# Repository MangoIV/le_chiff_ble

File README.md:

# le_chiff_ble
## What is this? 
This is a drop-in replacement PCB for [tominabox1's](https://github.com/tominabox1) Le Chiffre keyboard, one of my all time favourite boards. I redesigned the existing PCB from top up and added bluetooth. 
Please be so kind and check out the [original repo](https://github.com/tominabox1/Le-Chiffre-Keyboard) and leave a star. This is where you can also find case files for this PCB. 

Some of the footprints are not taken from the standard kicad libraries, huge thanks to [foostan](https://github.com/foostan) for making the awesome "kbd" library and to [ai03](https://ai03.com/) for their super nice footprint libraries, the minew symbol and footprints are by [oreore](https://github.com/ogatatsu).

All graphics on my PCB are hand drawn and belong to no-one but me. 

There are two PCBs in this repo one
- with hotswap, no silkscreen, see kicad/le_chiff_ble_hotswap
- without hotswap, with silkscreen, see kicad/le_chiff_ble

**I do not take any responsibility for what you do with the files supplied here in any way. Neither do I guarantee they're working for whatever purpose you intend ot use them.**

## State of the project
### implemented
- charging circuit is working
- MCU connects via bluetooth and USB
- all features have been tested and are working, including OLED and Encoder
- a working zmk firmware can be found [here](https://github.com/MangoIV/le_chiff_ble_config).
### open tasks
- the widgets in zmk for the OLED are still very basic, I'd like to do something to make them look better, this will be added after I finished and uploaded the firmware 
## How can I obtain one
- Gerbers are supplied, be free to order them from the PCB manufacturer you prefer.
### you will need parts: 
1. **Resistors, footprint is 0805:**
  - 1x 2M
  - 1x 1M
  - 1x 806k
  - 1x 100k
  - 2x 5.1k
  - 1x 1.8k 
  - 3x 1k
  - 2x 100
  - 1x 2.1
2. **Capacitors, footprint is 0805**
  - 4x 10uF
  - 2x 1uF
  - 2x 0.1uF
  - 1x 1nF
3. **Diodes**
  - 35x SOD123 for the switches and encoder
  - 1x Schottky, SOD323, should be low voltage drop
  - either 2x in switch LEDs or 2x 0805 SMD LEDs for the charging indicator
4. 1x PMOS, A03401A
5. 1x battery management chip, TP4056, footprint is SOP-8-PP
6. 1x LDO, XC6206PxxMR
7. 1x usblc6, footprint is sot-23-6
8. 1x 500mA Fuse, footprint is 1206/ 3216Metric
9. 1x battery protection IC DW01A, footprint is sot-23-6
10. 1x two nmos with gates connects FS8205, footprint is sot-23-6
11. 1x Minew MS88SF2, be careful to choose the version with nrF52840, there's also another version with the same name which won't work
12. 1x USB type c port, 12 pin
13. 1x MSK-12C02 smd toggle switch
14. 1x SW SPST TL3342 push switch for reset
15. 34-35 MX/alps/choc switches depending on whether you use the encoder or not
16. Battery connector with 1.25mm pitch, choose whichever you're fine with
17. optional: 1x Encoder, 1x 128x32 OLED
## How do I build one? 
- solder all components
- flash bootloader (I liked [this one](https://github.com/adafruit/Adafruit_nRF52_Bootloader) a lot, it's fairly easy to modify to your needs, e.g. the name the board will appear with in bootloader mode)
- plug into PC and test whether everything is working, flash Firmware 
- the firmware can be forked from [here](https://github.com/MangoIV/le_chiff_ble_config), just adjust the `.keymap` file, push, let GitHub Actions build it for you, download, done
- plug in battery, plug in PC again to unlock DW01A (this needs to be done everytime you physically disconnect the PCB from the battery)
- be careful to adjust resistor value of the tp4056 when you take different battery sizes, I chose 1Ah which works fine with the specified resistor values
- verify charging and bluetooth works 
- continue building as if this was a "normal" chiffre

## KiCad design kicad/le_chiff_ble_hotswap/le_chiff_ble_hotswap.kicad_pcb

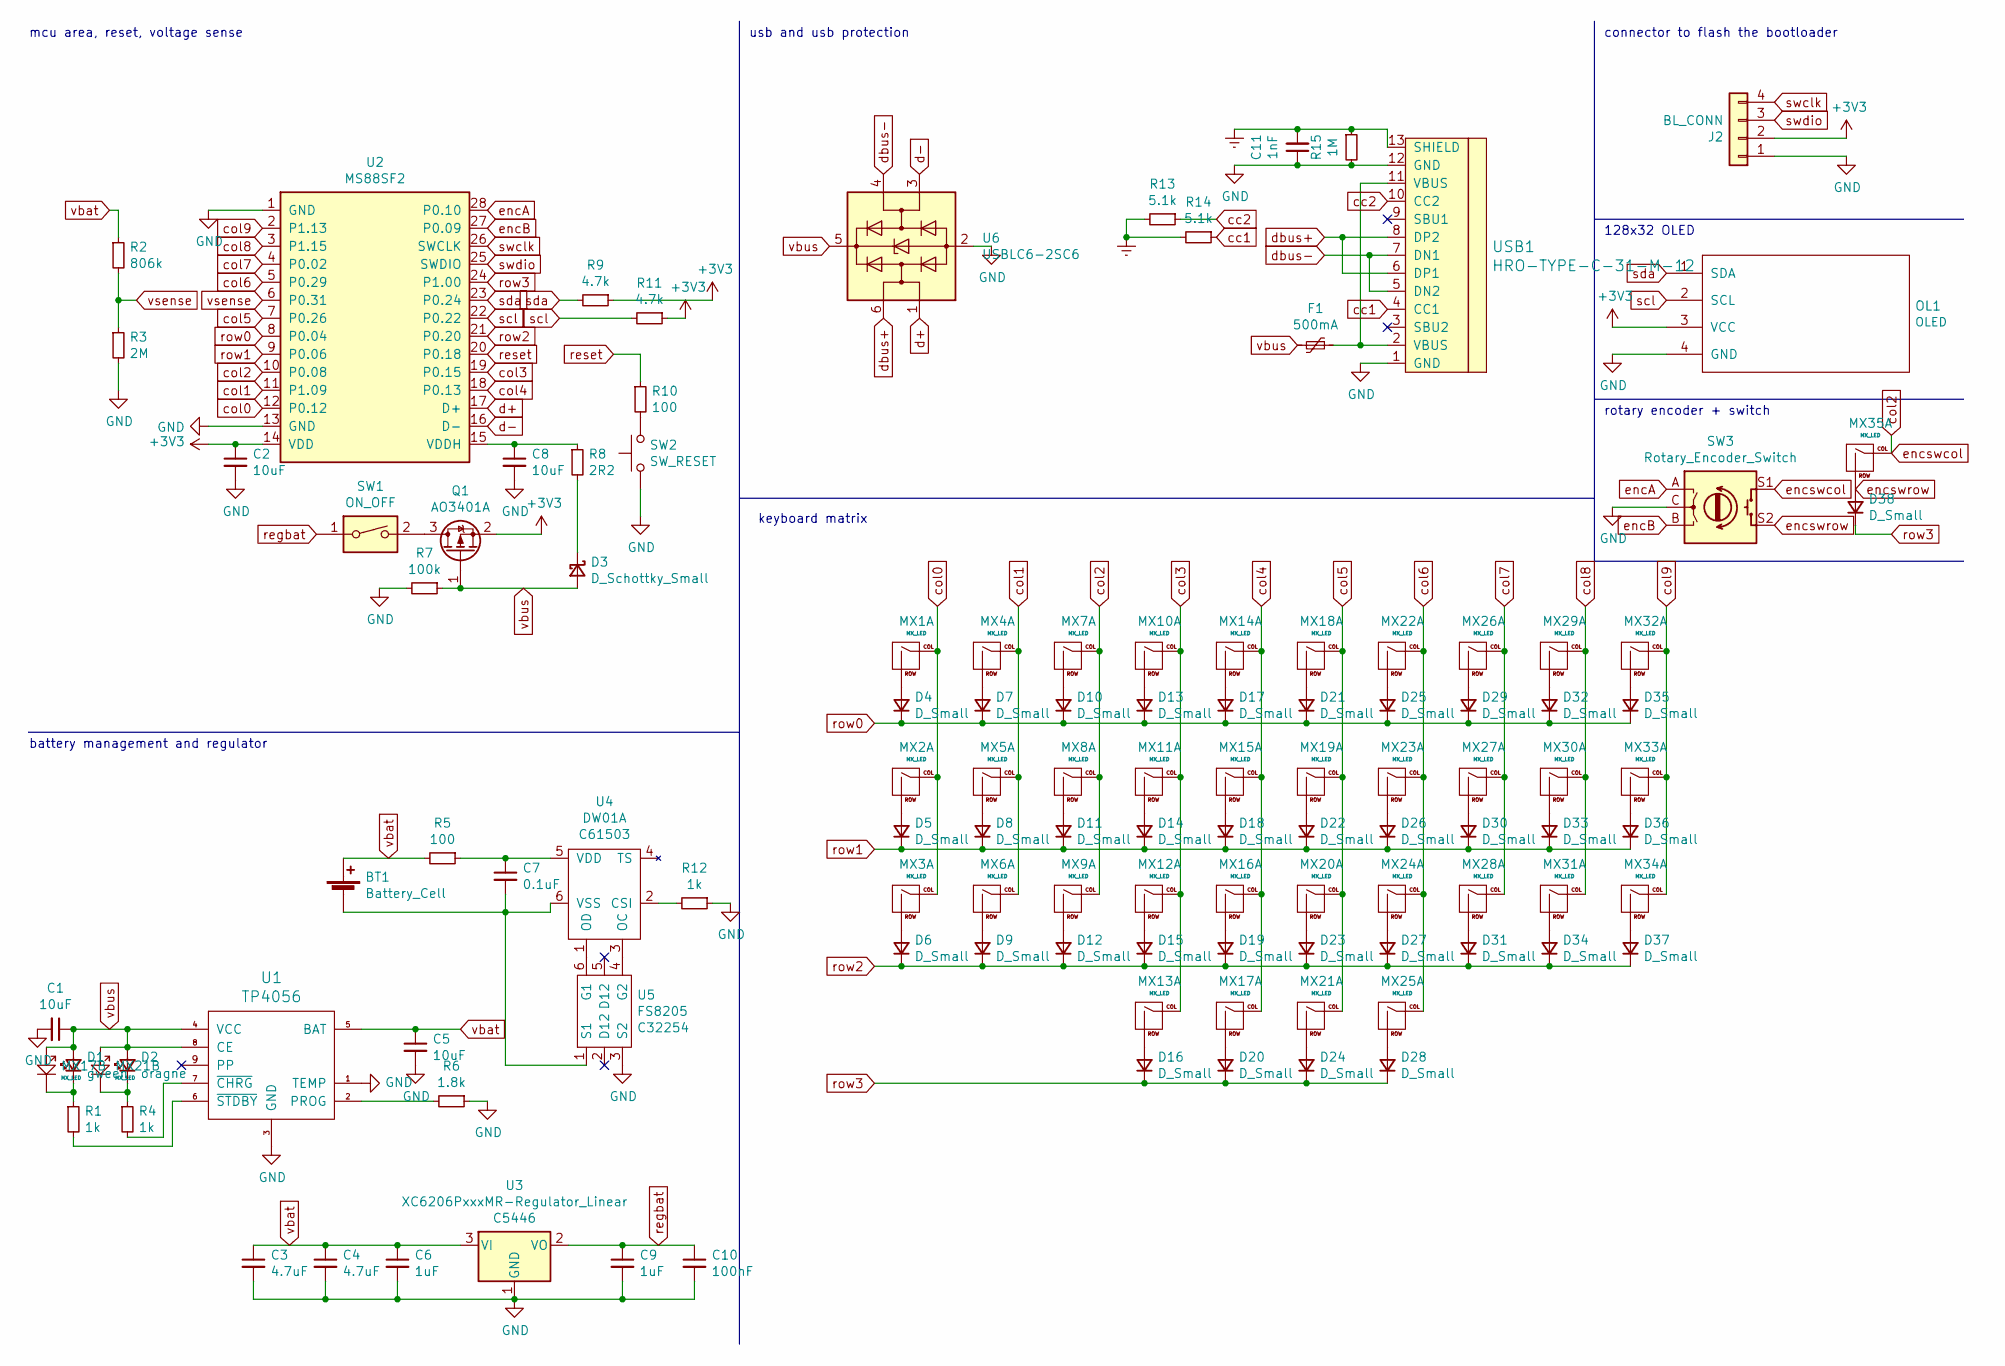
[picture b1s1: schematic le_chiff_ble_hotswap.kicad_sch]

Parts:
BT1: Battery_Cell; Molex_PicoBlade_53048-0210_1x02_P1.25mm_Horizontal
C1, C2, C5, C8: 10uF; C_0805_2012Metric
C3, C4: 4.7uF; C_0805_2012Metric
C6, C9: 1uF; C_0805_2012Metric
C7: 0.1uF; C_0805_2012Metric
C10: 100nF; C_0805_2012Metric
C11: 1nF; C_0805_2012Metric
D1: gween; D_0805_2012Metric
D2: oragne; D_0805_2012Metric
D3: D_Schottky_Small; D_SOD-323_HandSoldering
D4, D5, D6, D7, D8, D9, D10, D11, D12, D13, D14, D15, D16, D17, D18, D19, D20, D21, D22, D23, D24, D25, D26, D27, D28, D29, D30, D31, D32, D33, D34, D35, D36, D37, D38: D_Small; D_SOD-123
F1: 500mA; Fuse_1206_3216Metric
J2: BL_CONN; PinHeader_1x04_P2.54mm_Vertical
MX1, MX2, MX3, MX4, MX5, MX6, MX7, MX8, MX9, MX10, MX11, MX12, MX13, MX14, MX15, MX16, MX18, MX19, MX20, MX22, MX23, MX24, MX25, MX26, MX27, MX28, MX29, MX30, MX31, MX32, MX33, MX34, MX35: MX_LED; MX-Alps-Choc-1U-NoLED
MX17, MX21: MX_LED; MX-Alps-Choc-2U-StabFlip
OL1: OLED; OLED_1side
Q1: AO3401A; SOT-23
R1, R4, R12: 1k; R_0805_2012Metric
R2: 806k; R_0805_2012Metric
R3: 2M; R_0805_2012Metric
R5, R10: 100; R_0805_2012Metric
R6: 1.8k; R_0805_2012Metric
R7: 100k; R_0805_2012Metric
R8: 2R2; R_0805_2012Metric
R9, R11: 4.7k; R_0805_2012Metric
R13, R14: 5.1k; R_0805_2012Metric
R15: 1M; R_0805_2012Metric
SW1: ON_OFF; switch_MSK-12C02_smd
SW2: SW_RESET; SW_SPST_TL3342
SW3: Rotary_Encoder_Switch; RotaryEncoder_EC11-no-legs
U1: TP4056; TP4056_SOP-8-PP
U2: MS88SF2; MINEW_MS88SF2
U3: XC6206PxxxMR-Regulator_Linear; SOT-23; LCSC C5446
U4: DW01A; SOT-23-6; LCSC C61503
U5: FS8205; SOT-23-6; LCSC C32254
U6: USBLC6-2SC6; SOT-23-6
USB1: HRO-TYPE-C-31-M-12; HRO-TYPE-C-31-M-12-Assembly

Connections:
+3V3: C2.1, J2.2, OL1.3 (VCC), Q1.2 (S), R9.1, R11.1, U2.14 (VDD)
Earth: C11.2, R13.2, R14.2, R15.1, USB1.13 (SHIELD)
GND: C1.2, C2.2, C3.2, C4.2, C5.2, C6.2, C8.2, C9.2, C10.2, C11.1, J2.1, OL1.4 (GND), R3.2, R6.1, R7.2, R12.1, R15.2, SW2.1, SW3.C, U1.1 (TEMP), U1.3 (GND), U2.1 (GND), U2.13 (GND), U3.1 (GND), U5.3 (S2), U6.2 (GND), USB1.1 (GND), USB1.12 (GND)
unnamed: BT1.2 (-), C7.2, U4.6 (VSS), U5.1 (S1)
unnamed: C7.1, R5.1, U4.5 (VDD)
unnamed: C8.1, R8.1, U2.15 (VDDH)
unnamed: D1.1 (K), MX17.4 (C), R1.1
unnamed: D2.1 (K), MX21.4 (C), R4.1
unnamed: D3.1 (K), R8.2
unnamed: D4.2 (A), MX1.2 (ROW)
unnamed: D5.2 (A), MX2.2 (ROW)
unnamed: D6.2 (A), MX3.2 (ROW)
unnamed: D7.2 (A), MX4.2 (ROW)
unnamed: D8.2 (A), MX5.2 (ROW)
unnamed: D9.2 (A), MX6.2 (ROW)
unnamed: D10.2 (A), MX7.2 (ROW)
unnamed: D11.2 (A), MX8.2 (ROW)
unnamed: D12.2 (A), MX9.2 (ROW)
unnamed: D13.2 (A), MX10.2 (ROW)
unnamed: D14.2 (A), MX11.2 (ROW)
unnamed: D15.2 (A), MX12.2 (ROW)
unnamed: D16.2 (A), MX13.2 (ROW)
unnamed: D17.2 (A), MX14.2 (ROW)
unnamed: D18.2 (A), MX15.2 (ROW)
unnamed: D19.2 (A), MX16.2 (ROW)
unnamed: D20.2 (A), MX17.2 (ROW)
unnamed: D21.2 (A), MX18.2 (ROW)
unnamed: D22.2 (A), MX19.2 (ROW)
unnamed: D23.2 (A), MX20.2 (ROW)
unnamed: D24.2 (A), MX21.2 (ROW)
unnamed: D25.2 (A), MX22.2 (ROW)
unnamed: D26.2 (A), MX23.2 (ROW)
unnamed: D27.2 (A), MX24.2 (ROW)
unnamed: D28.2 (A), MX25.2 (ROW)
unnamed: D29.2 (A), MX26.2 (ROW)
unnamed: D30.2 (A), MX27.2 (ROW)
unnamed: D31.2 (A), MX28.2 (ROW)
unnamed: D32.2 (A), MX29.2 (ROW)
unnamed: D33.2 (A), MX30.2 (ROW)
unnamed: D34.2 (A), MX31.2 (ROW)
unnamed: D35.2 (A), MX32.2 (ROW)
unnamed: D36.2 (A), MX33.2 (ROW)
unnamed: D37.2 (A), MX34.2 (ROW)
unnamed: F1.1, USB1.2 (VBUS), USB1.11 (VBUS)
unnamed: Q1.3 (D), SW1.2
unnamed: R1.2, U1.6 (~STDBY)
unnamed: R4.2, U1.7 (~CHRG)
unnamed: R6.2, U1.2 (PROG)
unnamed: R10.2, SW2.2
unnamed: R12.2, U4.2 (CSI)
unnamed: U4.1 (OD), U5.6 (G1)
unnamed: U4.3 (OC), U5.4 (G2)
cc1: R14.1, USB1.4 (CC1)
cc2: R13.1, USB1.10 (CC2)
col0: MX1.1 (COL), MX2.1 (COL), MX3.1 (COL), U2.12 (P0.12)
col1: MX4.1 (COL), MX5.1 (COL), MX6.1 (COL), U2.11 (P1.09)
col2: MX7.1 (COL), MX8.1 (COL), MX9.1 (COL), MX35.1 (COL), SW3.S1, U2.10 (P0.08)
col3: MX10.1 (COL), MX11.1 (COL), MX12.1 (COL), MX13.1 (COL), U2.19 (P0.15)
col4: MX14.1 (COL), MX15.1 (COL), MX16.1 (COL), MX17.1 (COL), U2.18 (P0.13)
col5: MX18.1 (COL), MX19.1 (COL), MX20.1 (COL), MX21.1 (COL), U2.7 (P0.26)
col6: MX22.1 (COL), MX23.1 (COL), MX24.1 (COL), MX25.1 (COL), U2.5 (P0.29)
col7: MX26.1 (COL), MX27.1 (COL), MX28.1 (COL), U2.4 (P0.02)
col8: MX29.1 (COL), MX30.1 (COL), MX31.1 (COL), U2.3 (P1.15)
col9: MX32.1 (COL), MX33.1 (COL), MX34.1 (COL), U2.2 (P1.13)
d+: U2.17 (D+), U6.1 (I/O1)
d-: U2.16 (D-), U6.3 (I/O2)
dbus+: U6.6 (I/O1), USB1.6 (DP1), USB1.8 (DP2)
dbus-: U6.4 (I/O2), USB1.5 (DN2), USB1.7 (DN1)
encA: SW3.A, U2.28 (P0.10)
encB: SW3.B, U2.27 (P0.09)
encswrow: D38.2 (A), MX35.2 (ROW), SW3.S2
regbat: C9.1, C10.1, SW1.1, U3.2 (VO)
reset: R10.1, U2.20 (P0.18)
row0: D4.1 (K), D7.1 (K), D10.1 (K), D13.1 (K), D17.1 (K), D21.1 (K), D25.1 (K), D29.1 (K), D32.1 (K), D35.1 (K), U2.8 (P0.04)
row1: D5.1 (K), D8.1 (K), D11.1 (K), D14.1 (K), D18.1 (K), D22.1 (K), D26.1 (K), D30.1 (K), D33.1 (K), D36.1 (K), U2.9 (P0.06)
row2: D6.1 (K), D9.1 (K), D12.1 (K), D15.1 (K), D19.1 (K), D23.1 (K), D27.1 (K), D31.1 (K), D34.1 (K), D37.1 (K), U2.21 (P0.20)
row3: D16.1 (K), D20.1 (K), D24.1 (K), D28.1 (K), D38.1 (K), U2.24 (P1.00)
scl: OL1.2 (SCL), R11.2, U2.22 (P0.22)
sda: OL1.1 (SDA), R9.2, U2.23 (P0.24)
swclk: J2.4, U2.26 (SWCLK)
swdio: J2.3, U2.25 (SWDIO)
vbat: BT1.1 (+), C3.1, C4.1, C5.1, C6.1, R2.1, R5.2, U1.5 (BAT), U3.3 (VI)
vbus: C1.1, D1.2 (A), D2.2 (A), D3.2 (A), F1.2, MX17.3 (A), MX21.3 (A), Q1.1 (G), R7.1, U1.4 (VCC), U1.8 (CE), U6.5 (VBUS)
vsense: R2.2, R3.1, U2.6 (P0.31)

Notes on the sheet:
mcu area, reset, voltage sense
keyboard matrix
battery management and regulator
128x32 OLED
usb and usb protection
rotary encoder + switch
connector to flash the bootloader

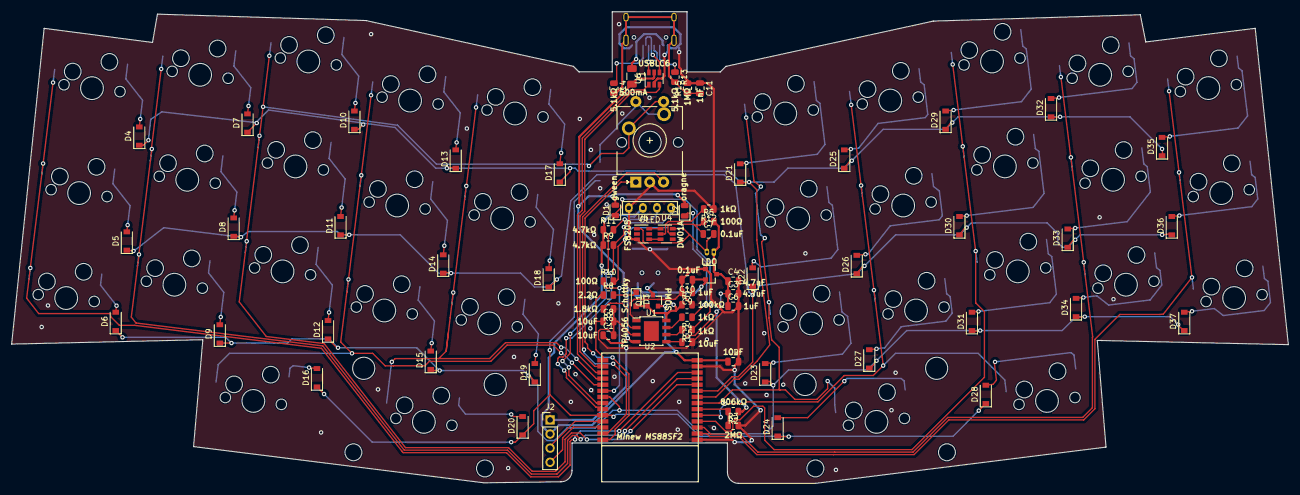
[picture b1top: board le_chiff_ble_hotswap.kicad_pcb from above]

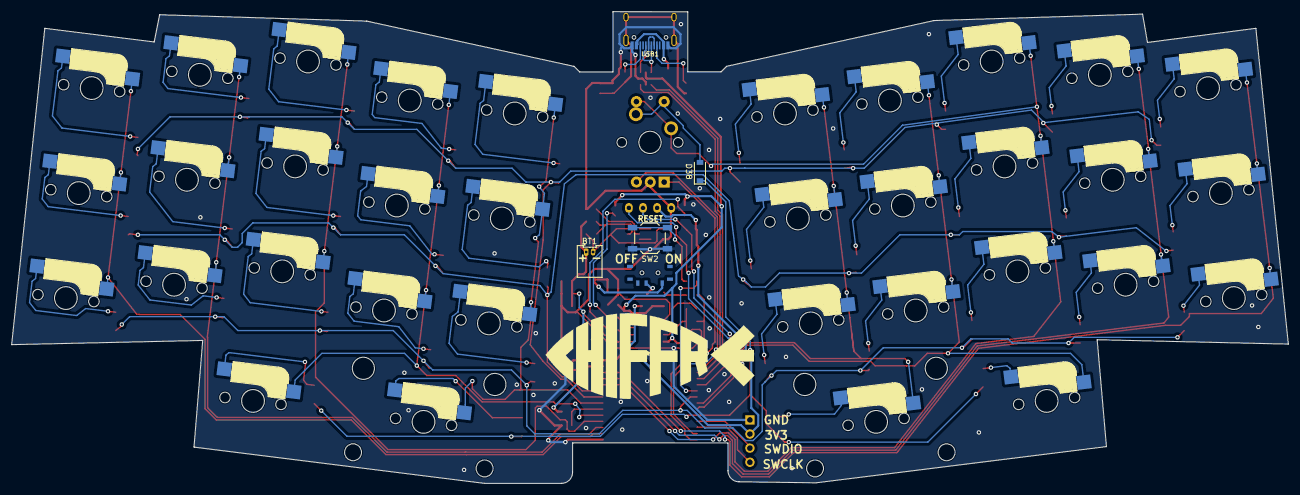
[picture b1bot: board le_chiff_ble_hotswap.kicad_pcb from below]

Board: 2 copper layers, 230.0 x 85.0 mm, 114 parts (5 on the bottom side), 84 nets.

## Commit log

2021-06-14 saved and have to commit
2021-06-14 finished the schematics and the PCB, maybe some silkscreen to come..
2021-08-02 added a screenshot of the mcu area
2021-08-05 changed paths to be relative
2021-09-12 started rerouting
2022-04-30 Create LICENSE
2024-01-28 added kicad project for hotswap board based on the work of weteor
2024-01-28 removed unnecessary files
2024-01-28 added kicad project for hotswap board based on the work of weteor (#3)
    added kicad project for hotswap board based on the work of weteor
2024-01-28 [chore] update README to show the existance of the hotswap PCB
2024-02-15 [chore] update README to show the existance of the hotswap PCB (#4)
